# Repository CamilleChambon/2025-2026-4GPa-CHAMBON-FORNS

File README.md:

# 2025-2026-4GPa-CHAMBON-FORNS-GIRAUD
## SOMMAIRE
*** 
  - [I. Description Projet Graphite](#description-projet-graphite)
  - [II. Livrables](#livrables)
  - [III. Matériel nécessaire](#matériel-nécessaire)
  - [IV. Electronique Analogique sous LTSpice](#electronique-analogique-sous-ltspice)
  - [V. Création du PCB sous KiCad](#creation-du-pcb-sous-kicad)
  - [VI. Réalisation du shield](#réalisation-du-shield)
  - [VII. Code Arduino](#code-arduino)
  - [VIII. Application Android](#application-android)
  - [IX. Banc de test](#banc-de-test)
  - [X. Datasheet](#datasheet)
  - [XI. Conclusion](#conclusion)

*** 

## Description Projet Graphite

&nbsp;&nbsp;&nbsp;&nbsp;&nbsp;&nbsp; Dans le cadre du cours "Du capteur au banc de test" de 4e année de Génie Physique, nous avons développé un capteur de contrainte basé sur une technologie low-tech. Comme présenté en introduction de la datasheet (cf. section X), le capteur Graphite est un capteur de contrainte résistif, composant passif qui fonctionne en mesurant les variations de résistance d'une fine couche de graphite appliquée au crayon à papier sur une surface papier. Lorsque ce dernier est déformé en tension ou en compression, la répartition des particules de graphite est modifiée, entraînant respectivement une hausse ou une baisse de sa résistance. Par la mesure de ces variations de résistance, il est possible de remonter à la variation de résistance. 

&nbsp;&nbsp;&nbsp;&nbsp;&nbsp;&nbsp; Le projet a consisté à développer un système complet autour de ce capteur : modélisation d'électronique analogique grâce au logiciel LTSpice, création d’un circuit imprimé (PCB) via Kicad, programmation avec Arduino, création d'une application mobile avec MIT App Inventor, et communication sans fil par Bluetooth, entre le téléphone et le système. Un banc de test a été spécialement réalisé en impression 3D pour évaluer les performances du capteur, grâce à des pièces circulaires de différents rayons de courbure. En ce qui concerne les codes, ayant rencontré des problèmes pour faire fonctionner l'écran OLED, nous avons rédigé deux codes distincts, l'un avec l'écran, l'autre sans.

## Livrables

  - Shield PCB compatible avec Arduino UNO, intégrant un capteur graphite, un amplificateur transimpédance, un module Bluetooth, un écran OLED, un flex sensor, un potentiomètre digital et un encodeur rotatoire.
  - Code Arduino assurant la lecture du capteur, l’affichage des données, la communication Bluetooth et l’interaction avec les composants.
  - Application Android réalisée sous MIT App Inventor pour visualiser les mesures transmises par Bluetooth.
  - Graphes des variations relatives de résistance du capteur graphite - en tension et en compression - et du flex sensor pour montrer les résultats obtenus sur le banc de test.
  - Datasheet du capteur de graphite, présentant ses principales caractéristiques, les résultats expérimentaux et un exemple de circuit d'utilisation courant.

## Matériel nécessaire

  - 1 carte Arduino Uno
  - 2 Résistances de 100kΩ
  - 1 Résistance de 1kΩ
  - 1 Potentiomètre digital MCP-41050
  - 2 Condensateurs 100nF
  - 1 Condensateur 1µF
  - 1 Amplificateur LTC1050
  - 1 Écran OLED01
  - 1 Module Bluetooth HC-05
  - 1 Encodeur rotatoire 

## Electronique Analogique sous LTSpice

Notre capteur graphite présente une résistance de l’ordre du gigaOhm, ce qui génère un courant de quelques pico à nano Ampères sous une tension de 5 V. Pour rendre ce signal exploitable par l’ADC d’une Arduino UNO, nous avons conçu un amplificateur transimpédance autour de l’AOP LTC1050. Après avoir modélisé le capteur et le montage sous LTspice pour déterminer la meilleure valeur de la résistance de rétroaction, nous avons ajouté trois étages de filtrage, fondés sur des filtres passe-bas, afin d'améliorer la qualité du signal en éliminant les hautes fréquences parasites, en atténuant le bruit secteur à 50 Hz et en supprimant les interférences liées à l’ADC.  

Ce circuit convertit ainsi le faible courant issu du capteur en une tension propre, directement lisible et traitable par la carte Arduino.

<p align="center">

<br>
<i>Circuit amplificateur transimpédance</i>
</p>

## Création du PCB sous KiCad

Lors de la phase de conception du shield, nous avons d’abord repris le gabarit d’une carte Arduino UNO dans KiCad (version 8.0) puis nous avons créé sur le même logiciel les symboles et empreintes manquants pour l'ensemble des composants que nous utiliserions, en respectant leurs dimensions et l’écartement des broches. Voici le schéma électrique de l'ensemble de notre montage :

<p align="center">

<br>
<i>Circuit électronique</i>
</p>

Une fois notre bibliothèque faite, nous avons assemblé le schéma électrique complet : chaque composant est relié selon le fonctionnement prévu. Sur la vue PCB, nous avons disposé les empreintes, effectué le routage des pistes, le tout afin d'optimiser l'espace disponible et de limiter le nombre de vias réalisés. Les résistances ont été positionnées verticalement sur le PCB. Enfin, nous avons ajouté un plan de masse pour relier certaines pistes au GND.
Voici notre PCB :

<p align="center">

<br>
<i>PCB</i>
</p>

Le résultat est un circuit imprimé prêt à être fabriqué et à recevoir chaque composant sur le shield Arduino UNO.

## Réalisation du Shield

Nous avons commencé par l’édition du masque de gravure de notre circuit imprimé (PCB) à l’aide du logiciel KiCad. Ensuite, nous avons procédé à l’insolation UV d’une plaquette recouverte d’une fine couche de cuivre et de résine photosensible. La plaquette a été immergée dans un révélateur chimique, ce qui permet d’éliminer la résine non exposée aux UV. Par la suite, on plonge la plaquette dans du perchlorure de fer pour graver les pistes du circuit en dissolvant le cuivre non protégé. Enfin, il faut un nettoyage à l’acétone pour retirer les résidus de résine restant sur la plaquette. A la fin de ce travail, nous avions notre circuit imprimé avec toutes les pistes tracées.
Une fois le PCB réalisé, nous n'avions plus qu'à le percer et y souder tous nos composants. Voici notre PCB final :

<p align="center">

<br>
<i>Notre PCB</i>
</p>

## Code Arduino 

Ce projet a été piloté par un [programme Arduino](Code%20Arduino). Pour utiliser les fonctions spéciales à tous les composants, nous avons installé les librairies Adafruit_SSD1306.h et Adfruit_GFX.h, SPI.h, Servo.h et SoftwareSerial.h.

Nous avons joint sur ce github deux codes distincts, avec des caractéristiques communes cependant.

Le code intitulé "code_final" est un code qui utilise les deux capteurs (flex et graphite), le servo-moteur, le module bluetooth et le potentiomètre. Il réalise deux étapes : une calibration, pour ramener à 2,5 V, la tension lue aux bornes du capteur graphite sans déformation, puis un cycle de mesure. Ces étapes sont lancées depuis les boutons de l'application Android (cf. infra). Lors d'un cycle de mesure, réalisé sur notre banc de test, le moteur avance d'un certain nombre de pas, puis l'on réalise une série de mesures dont on fait la moyenne pour obtenir une valeur stable, que l'on affiche ensuite sur l'application. Puis, le moteur avance de nouveau, et ainsi de suite. Plusieurs paramètres peuvent être réglés sur l'application Android :
- l'angle est la plage angulaire totale couverte par le servo-moteur;
- le nombre de mesures est le nombre de mesures sucessives que l'on réalise pour calculer une moyenne *sur une seule valeur de déformation* ;
- le nombre de pas correspond au nombre de points que l'on va afficher au final, c'est-à-dire, le nombre de mesures effectives réalisées.

Le code appelé "main" repose sur le même principe, bien qu'il ne présente pas d'étape de calibration. Cependant, il présente par ailleurs des menus affichés sur l'écran OLED permettant de régler les paramètres précisés supra, et utilise l'encodeur rotatoire comme moyen de se déplacer dans ces menus. Il est associé à un programme Python récupérant les données pour les afficher dans des graphiques.

## Application Android

Nous avons conçu une application Android en utilisant la plateforme MIT App Inventor. Cette application permet de recevoir les données de la carte Arduino via une connexion Bluetooth en utilisant le module HC-05 qui se trouve sur notre PCB. Après la connexion bluetooth, l'application nous donne en temps réel la valeur de la résistance du capteur graphite et trace sa courbe en fonction du temps sur un graphique. Vous la trouverez [Application MIT_App_Inventor](https://github.com/CamilleChambon/2025-2026-4GPa-CHAMBON-FORNS/tree/main/Application%20MIT_App_Inventor).

## Banc de test

Après avoir réalisé le montage électrique complet, ainsi que les parties softwares adéquates, il était nécessaire de tester notre capteur ainsi que le capteur commercial pour pouvoir les comparer. Pour cela, nous avons utilisé le banc de test ci-dessous, constitué de pièces circulaires de différents rayons de courbure (2 cm, 3 cm, 4 cm, 5 cm).

<p align="center">

<br>
<i>Banc de test utilisé</i>
</p>

Pour toutes les mesures, la résistance du potentiomètre digital était déterminée par la fonction de calibration. En ce qui concerne le capteur graphite, nous déposions du graphite issu de crayons HB, 3B et B. Nous n'avons pas réussi à obtenir des valeurs convenables avec des crayons plus durs.

Le principe du test est de poser le capteur et le flex sensor et de le tordre petit à petit à l'aide des pales du moteur qui tournent. Cela permet d'obtenir les valeurs de résistance en fonction de la déformation appliquée.

Pour nos calculs, les valeurs qui nous intéressent sont la variation relative de résitance ()
en fonction de la déformation (). 

Voici les courbes caractéristiques du capteur graphite, en tension et en compression : 

<p align="center">

<br>
</p>

<p align="center">

<br>
</p>

Et ci-dessous la caractéristique du flex sensor en tension : 

<p align="center">

<br>
</p>

Nous remarquons que la résistance évolue lorsque le capteur graphite est soumis à une déformation. En tension, la résistance augmente, tandis qu'en compression, elle diminue. Ce phénomène s'explique par le rapprochement des atomes lors de la compression, facilitant ainsi le passage du courant. Lors de la tension, les atomes s'éloignent, le courant a alors plus de mal pour passer. Les résultats montrent aussi que le type de crayon utilisé influence les valeurs de résistance mesurées. 

La capacité de déformation en compression du capteur graphite n'est pas très fiable selon nos résulats. Le modèle linéaire attendu s'éloigne de la caractéristique sur les grosses déformations. Ceci peut être en partie dû au frottement du graphite sur le banc de test, qui peut perturber l'agencement des atomes et ainsi les mesures réalisées. 

Ces résultats expérimentaux permettent de conclure que le capteur commercial est globalement plus sensible à la déformation que les capteurs en graphite, même si cette dernière est acceptable. De plus, il possède une certaine robustesse contrairement aux capteurs en papier : ceux-ci sont fragiles et n'importe quel contact peut altérer le gtaphite déposé. Le nombre d'utilisation est aussi limité, entre 3 et 5 séries de tests pour la plupart. Au-delà, les variations de résistance étaient très aléatoires et parfois inexistantes. Il était également nécessaire de déposer une grande quantité de graphite sur le papier pour pouvoir mesurer une résistance, notamment avec des crayons gras. 

## Datasheet

La datasheet de notre capteur est disponible [ici](Datasheet).

## Conclusion

Grâce à la série d'étapes amenant aux tests réalisés sur les deux capteurs, nous pouvons répondre à la question posée initialement, à savoir : le capteur graphite est industrialisable ou non ? 

Comme mentionné dans la partie [IX. Banc de test](#banc-de-test), les résultats montrent que le capteur commercial possède plusieurs avantages par rapport au capteur graphène. Il est plus fiable, plus durable et moins contraignant. Ces éléments peuvent rendre une commercialisation à grande échelle plus complexe dans l’état actuel du prototype.

Néanmoins, le capteur graphite demeure une option particulièrement pertinente dans certains contextes d’usage. Sa sensibilité s’est révélée plus qu’acceptable, et il est capable d’effectuer des mesures en compression, ce qui confirme la viabilité du concept. Pour des applications ponctuelles, rapides ou à usage unique, il constitue une alternative crédible et efficace.

Par ailleurs, ce capteur présente des atouts importants liés à sa philosophie de conception : son faible coût, sa simplicité de fabrication et son caractère low-tech le rendent particulièrement accessible. Utilisant des matériaux simples et peu transformés, il s’inscrit également dans une démarche plus sobre et écologique que certaines solutions commerciales plus complexes. Il conserve donc un réel intérêt.

Des pistes d’amélioration restent envisageables, notamment pour renforcer ses performances en compression (par exemple via une protection du graphite à l’aide d’un gel ou d’un matériau souple adapté) tout en conservant l’accessibilité et la simplicité qui font sa force. L’enjeu serait ainsi d’améliorer sa robustesse sans compromettre son aspect économique et durable.

Ce projet fut particulièrement enrichissant, car il nous a permis de concevoir à la fois les parties software et hardware d’un capteur, puis de le caractériser expérimentalement et d’élaborer une datasheet. Les différentes étapes du projet nous ont permis d’acquérir de nouvelles connaissances et compétences, que nous serons probablement amenés à mobiliser dans notre future carrière d’ingénieur physicien. Nous remercions nos professeurs pour leur accompagnement et pour nous avoir proposé ce projet tout au long du semestre.

Vous pouvez nous contacter si vous avez la moindre question :
- Timothy FORNS : forns@insa-toulouse.fr
- Camille CHAMBON : chambo@insa-toulouse.fr
- Faustine GIRAUD : girau@insa-toulouse.fr

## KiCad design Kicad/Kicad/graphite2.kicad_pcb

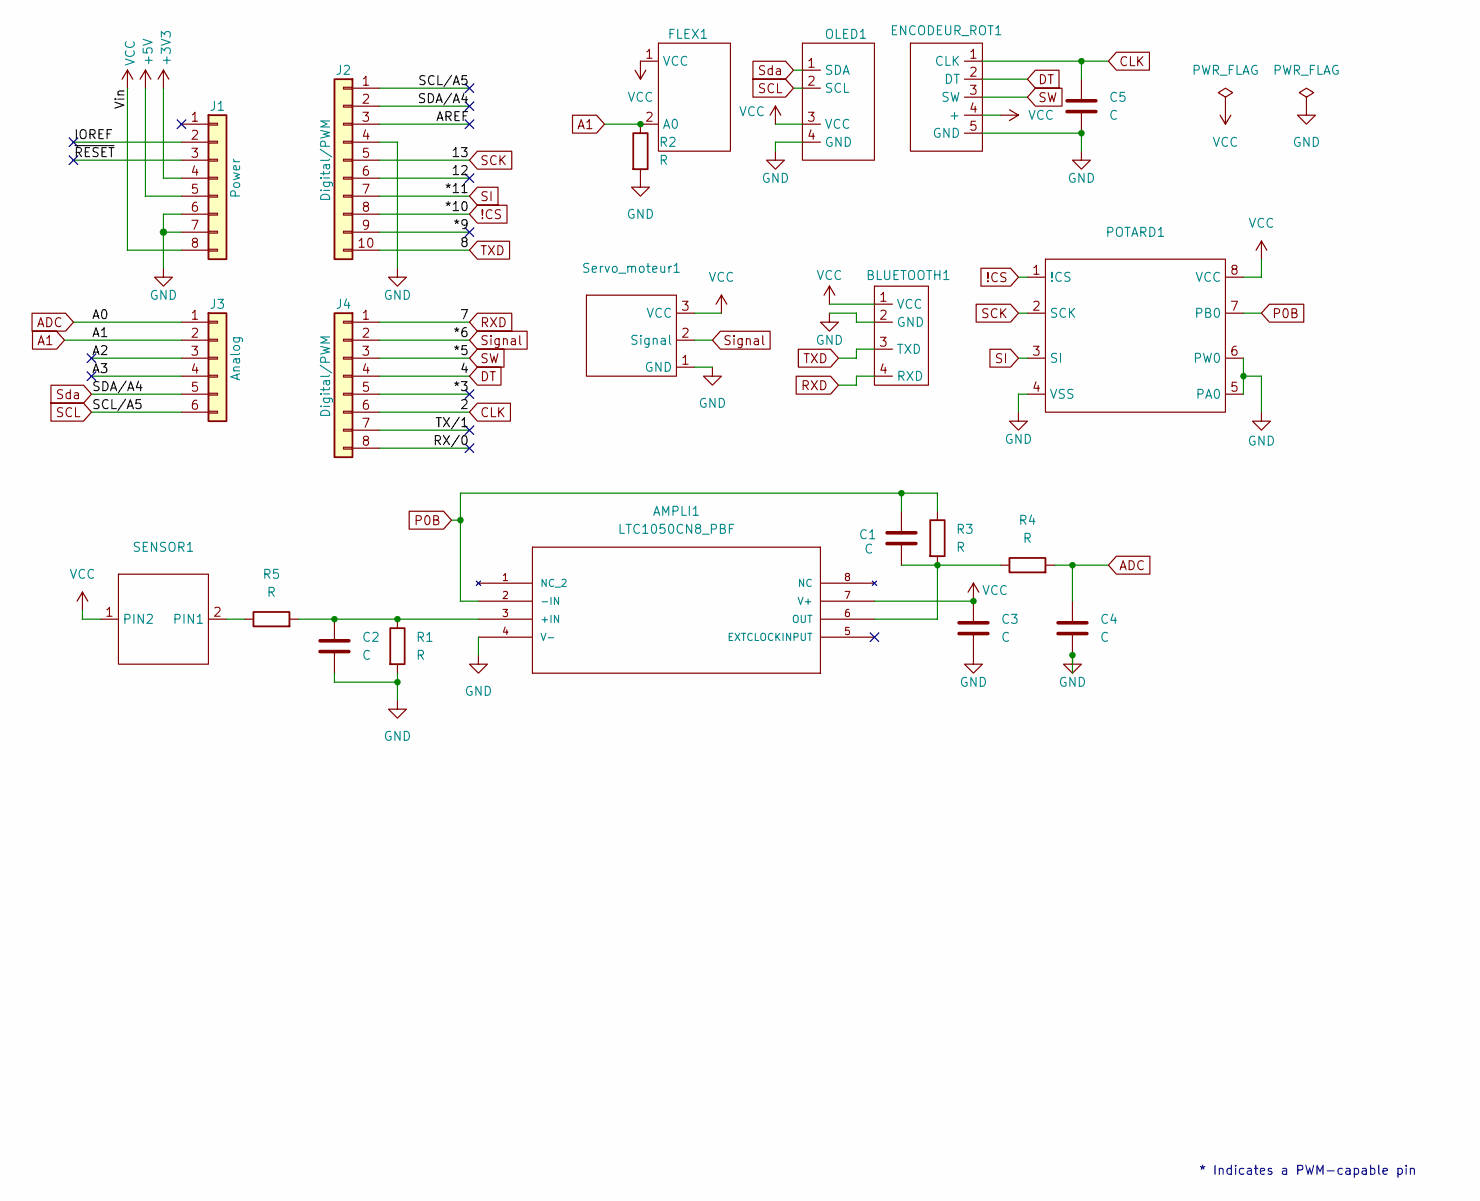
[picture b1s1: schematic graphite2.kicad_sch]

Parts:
AMPLI1: LTC1050CN8_PBF; PDIP-8_N; MANUFACTURER_PART_NUMBER ltc1050cn8
BLUETOOTH1: Bluetooth_HC05
C1, C2, C3, C4, C5: C
ENCODEUR_ROT1: ENCODEUR_empreinte
FLEX1: FLEX
J1: Power; PinSocket_1x08_P2.54mm_Vertical
J2: Digital/PWM; PinSocket_1x10_P2.54mm_Vertical
J3: Analog; PinSocket_1x06_P2.54mm_Vertical
J4: Digital/PWM; PinSocket_1x08_P2.54mm_Vertical
OLED1: OLED_empreinte
POTARD1: POTENTIO MCP
R1, R2, R3, R4, R5: R
SENSOR1: SENSOR
Servo_moteur1: SERVOMOTEUR

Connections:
!CS: J2.8, POTARD1.1 (!CS)
+3V3: J1.4
+5V: J1.5
/12: J2.6
/*3: J4.5
/*9: J2.9
/A2: J3.3
/A3: J3.4
/AREF: J2.3
/IOREF: J1.2
/RX/0: J4.8
/TX/1: J4.7
/~RESET: J1.3
A1: FLEX1.2 (A0), J3.2, R2.1
ADC: C4.1, J3.1, R4.2
CLK: C5.1, ENCODEUR_ROT1.1 (CLK), J4.6
DT: ENCODEUR_ROT1.2 (DT), J4.4
GND: AMPLI1.4 (V-), BLUETOOTH1.2 (GND), C2.2, C3.2, C4.2, C5.2, ENCODEUR_ROT1.5 (GND), J1.6, J1.7, J2.4, OLED1.4 (GND), POTARD1.4 (VSS), POTARD1.5 (PA0), POTARD1.6 (PW0), R1.2, R2.2, Servo_moteur1.1 (GND)
unnamed: AMPLI1.3 (+IN), C2.1, R1.1, R5.2
unnamed: AMPLI1.6 (OUT), C1.2, R3.2, R4.1
unnamed: R5.1, SENSOR1.2 (PIN1)
P0B: AMPLI1.2 (-IN), C1.1, POTARD1.7 (PB0), R3.1
RXD: BLUETOOTH1.4 (RXD), J4.1
SCK: J2.5, POTARD1.2 (SCK)
SCL: J2.1, J3.6, OLED1.2 (SCL)
SI: J2.7, POTARD1.3 (SI)
SW: ENCODEUR_ROT1.3 (SW), J4.3
Sda: J2.2, J3.5, OLED1.1 (SDA)
Signal: J4.2, Servo_moteur1.2 (Signal)
TXD: BLUETOOTH1.3 (TXD), J2.10
VCC: AMPLI1.7 (V+), BLUETOOTH1.1 (VCC), C3.1, ENCODEUR_ROT1.4 (+), FLEX1.1 (VCC), J1.8, OLED1.3 (VCC), POTARD1.8 (VCC), SENSOR1.1 (PIN2), Servo_moteur1.3 (VCC)

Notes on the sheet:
* Indicates a PWM-capable pin

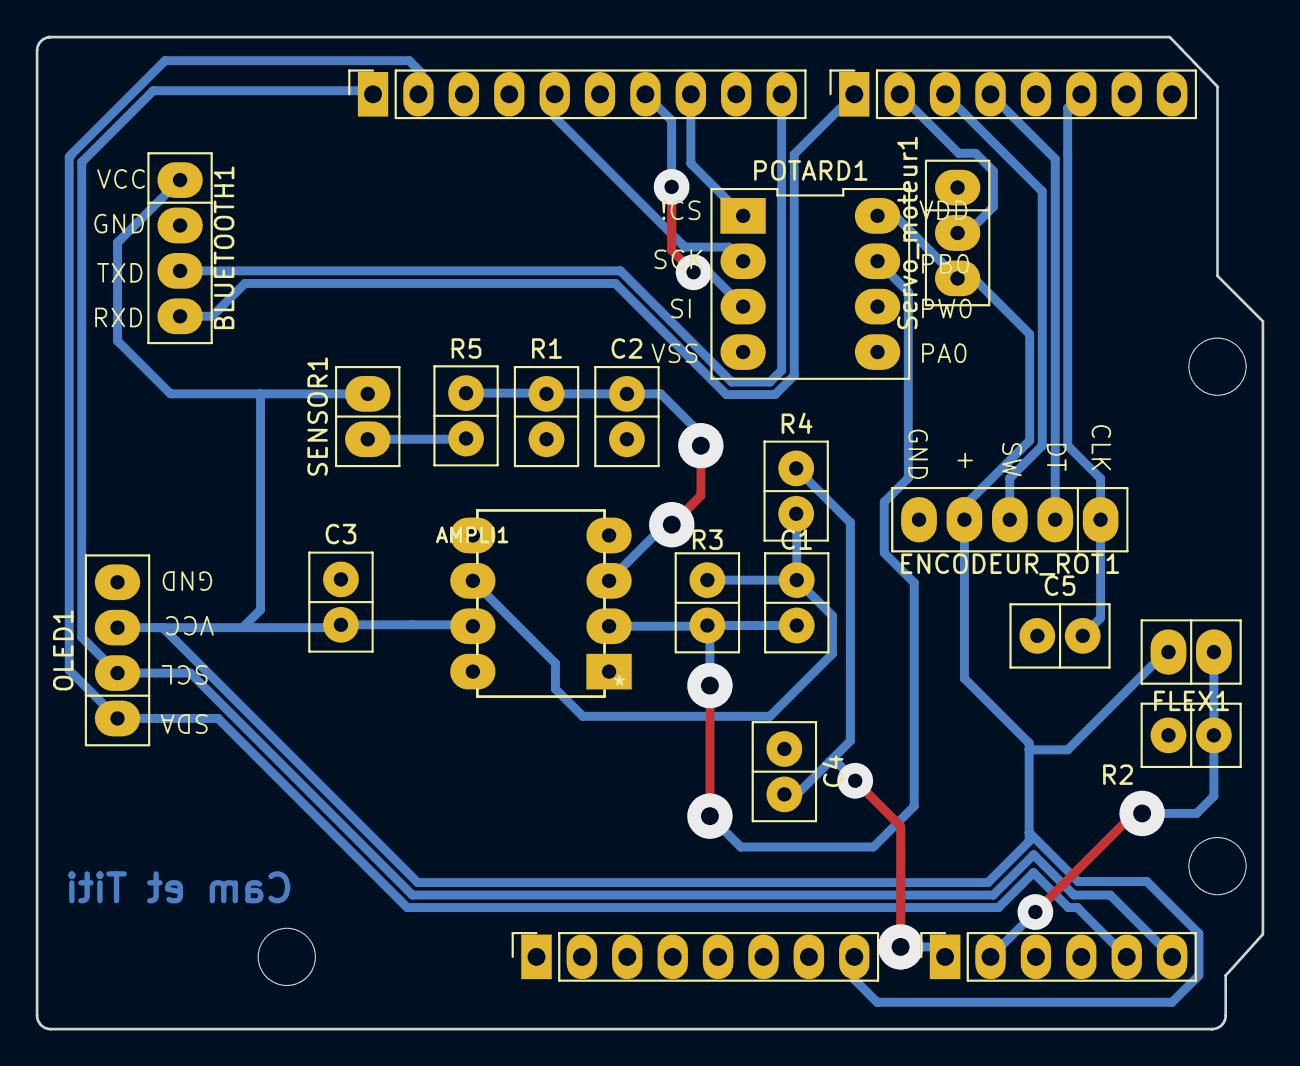
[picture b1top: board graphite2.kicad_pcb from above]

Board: 2 copper layers, 68.6 x 55.5 mm, 25 parts (0 on the bottom side), 19 nets.

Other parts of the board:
MH2, MH3, MH4: MountingHole_3.2mm

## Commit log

2026-03-05 TEST CAMILLE
2026-03-07 Test de nouvelle branche
2026-03-07 Code Capteur OLED
2026-05-15 Update README.md
    change
2026-05-15 Create Hello_world
2026-05-15 Rename bas-Corps.step to Banc_de_test/bas-Corps.step
2026-05-15 Rename adaptateur boite-Body.step to Banc_de_test/adaptateur boite-Body.step
2026-05-15 Rename brasù-Body.step to Banc_de_test/bras-Body.step
2026-05-15 Rename fixe_bras-Body.step to Banc_de_test/fixe_bras-Body.step
2026-05-15 Rename pièce_guidage_20mm-Body.step to Banc_de_test/pièce_guidage_20mm-Body.step
2026-05-15 Rename pièce_guidage_30mm-Body.step to Banc_de_test/pièce_guidage_30mm-Body.step
2026-05-15 Rename pièce_guidage_40mm-Body.step to Banc_de_test/pièce_guidage_40mm-Body.step
2026-05-15 Rename pièce_guidage_50mm-Body.step to Banc_de_test/pièce_guidage_50mm-Body.step
2026-05-15 Create Datasheet
2026-05-15 Create APp
2026-05-15 Create Hihihi
2026-05-15 Rename MAIN_2_0.ino to Code_final.ino
2026-05-15 Create h
2026-05-15 Create hlfrr
2026-05-15 Add project presentation section to README
2026-05-15 Create fvv
2026-05-15 Rename Testeuh.apk to Application.apk
2026-05-17 Revise README for clarity on PCB and sensor testing
    Updated the README to clarify the design process and results of the PCB and sensor tests, including changes to the Arduino code and Android application details.

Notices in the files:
parts and their libraries:
COPYRIGHT: Copyright C 2016 Accelerated Designs. All rights reserved
